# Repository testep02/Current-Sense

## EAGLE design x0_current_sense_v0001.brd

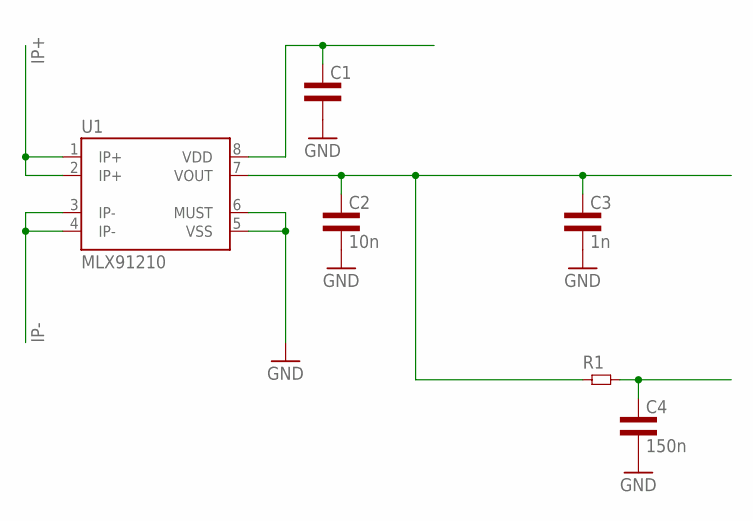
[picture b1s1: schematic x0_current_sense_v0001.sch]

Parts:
C1: CAP0603L3; 0603L3
C2: 10n; 0603L3
C3: 1n; 0603L3
C4: 150n; 0603L3
R1: RES0603L3; 0603L3
U1: MLX91210; SOIC-8

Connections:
GND: C1.P$2 (2), C2.P$2 (2), C3.P$2 (2), C4.P$2 (2), U1.5 (VSS), U1.6 (MUST)
IP+: U1.1 (IP+), U1.2 (IP+)
IP-: U1.3 (IP-), U1.4 (IP-)
unnamed: C4.P$1 (1), R1.P$2 (2)
unnamed: C1.P$1 (1), U1.8 (VDD)
unnamed: C2.P$1 (1), C3.P$1 (1), R1.P$1 (1), U1.7 (VOUT)

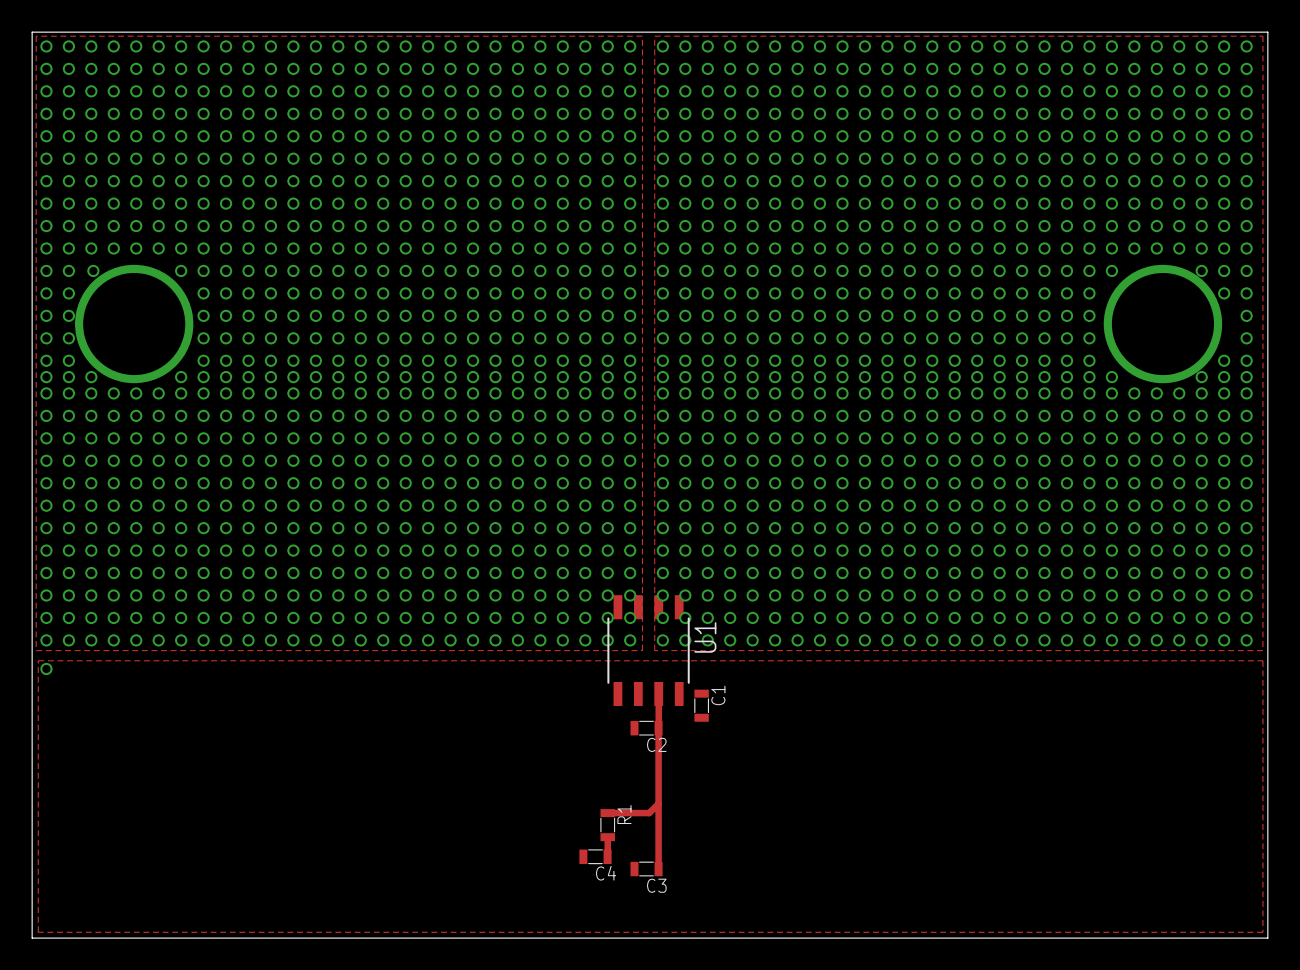
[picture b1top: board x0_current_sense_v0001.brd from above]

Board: 4 copper layers, 76.9 x 56.4 mm, 6 parts (0 on the bottom side), 6 nets.

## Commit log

2017-03-01 Initial commit of Vape - X0 - Current Sense board

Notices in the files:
parts and their libraries:
SparkFun-Aesthetics: Licensing: CC v3.0 Share-Alike You are welcome to use this library for commercial purposes.
